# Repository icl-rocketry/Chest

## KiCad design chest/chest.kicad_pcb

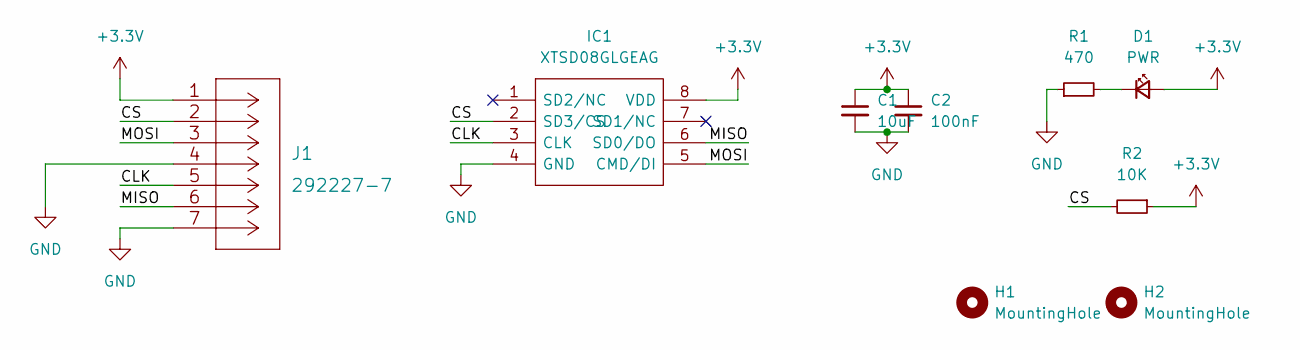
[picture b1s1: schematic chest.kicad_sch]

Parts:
C1: 10uF; C_0603_1608Metric
C2: 100nF; C_0603_1608Metric
D1: PWR; LED_0603_1608Metric
H1, H2: MountingHole; MountingHole_2.7mm_M2.5_DIN965
IC1: XTSD08GLGEAG; SON127P800X600X95-8N; Manufacturer_Part_Number XTSD08GLGEAG
J1: 292227-7
R1: 470; R_0603_1608Metric
R2: 10K; R_0603_1608Metric

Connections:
+3V3: C1.1, C2.1, D1.2 (A), IC1.8 (VDD), J1.1, R2.1
/CLK: IC1.3 (CLK), J1.5
/CS: IC1.2 (SD3/CS), J1.2, R2.2
/MISO: IC1.6 (SD0/DO), J1.6
/MOSI: IC1.5 (CMD/DI), J1.3
GND: C1.2, C2.2, IC1.4 (GND), J1.4, J1.7, R1.1
unnamed: D1.1 (K), R1.2

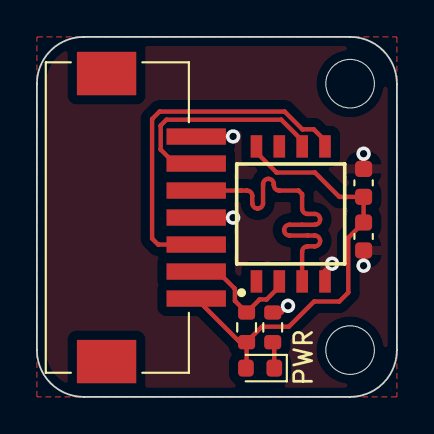
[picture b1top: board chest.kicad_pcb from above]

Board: 2 copper layers, 20.0 x 20.0 mm, 9 parts (0 on the bottom side), 7 nets.

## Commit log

2022-05-14 Chest

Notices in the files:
parts and their libraries:
Copyright 2021 Accelerated Designs. All rights reserved.
